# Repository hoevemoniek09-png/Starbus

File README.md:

I wanted to get into tech so as a first project I made a starbie. My Starbie is a bursting star that's why it's a starburst.

it's really pointy. 

This is my first time participating in something from hackclub and also making anything software/hardware related.

Starting with the schematic I just followed the starbie guide. 
In the PCB editor I gave my starbie a different shape, turning it into a bursting star. I traced according to the shape of it and added little stars to the plate. 

In arduino I took over the code from the starbie guide and changed the shape of my character to a little star.

Also adding a sparkle trail to give it more personality.

For parts, I mostly looked on Tinytronics since they have everything in stock.

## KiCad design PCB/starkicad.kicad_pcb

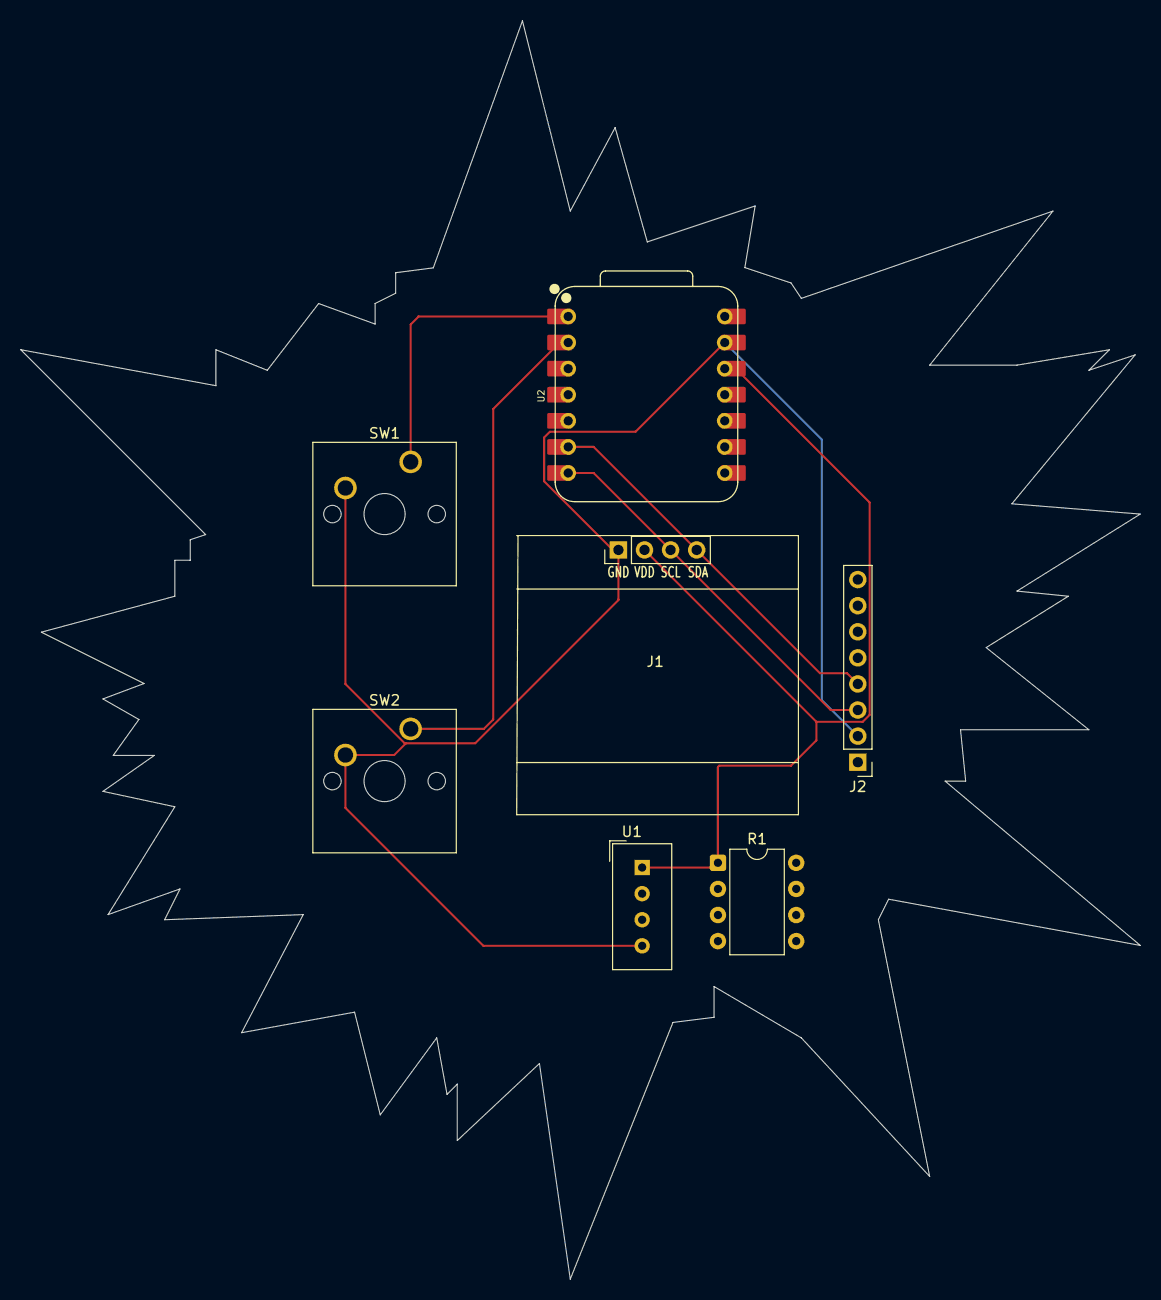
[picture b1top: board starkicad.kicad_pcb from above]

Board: 2 copper layers, 109.0 x 122.5 mm, 7 parts (0 on the bottom side), 6 nets.

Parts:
J1: Conn_01x04_Pin; Display_128x64_096_I2C
J2: Conn_01x08_Pin; PinHeader_1x08_P2.54mm_Vertical
R1: 10K; DIP-8_W7.62mm
SW1, SW2: SW_Push; SW_Cherry_MX_1.00u_PCB
U1: DHT11; Aosong_DHT11_5.5x12.0_P2.54mm
U2: XIAO-ESP32-C3-SMD; XIAO-ESP32-C6-DIP

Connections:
+3.3V: J1.2, R1.1, U1.1 (VDD), U2.12 (3V3_OUT)
/SCL: J1.3, J2.3, U2.7 (D6)
/SDA: J1.4, J2.4, U2.6 (D5)
GND: J1.1, J2.2, SW1.2, SW2.2, U1.4 (GND), U2.13 (GND)
unnamed: SW1.1, U2.1 (D0)
unnamed: SW2.1, U2.2 (D1)
